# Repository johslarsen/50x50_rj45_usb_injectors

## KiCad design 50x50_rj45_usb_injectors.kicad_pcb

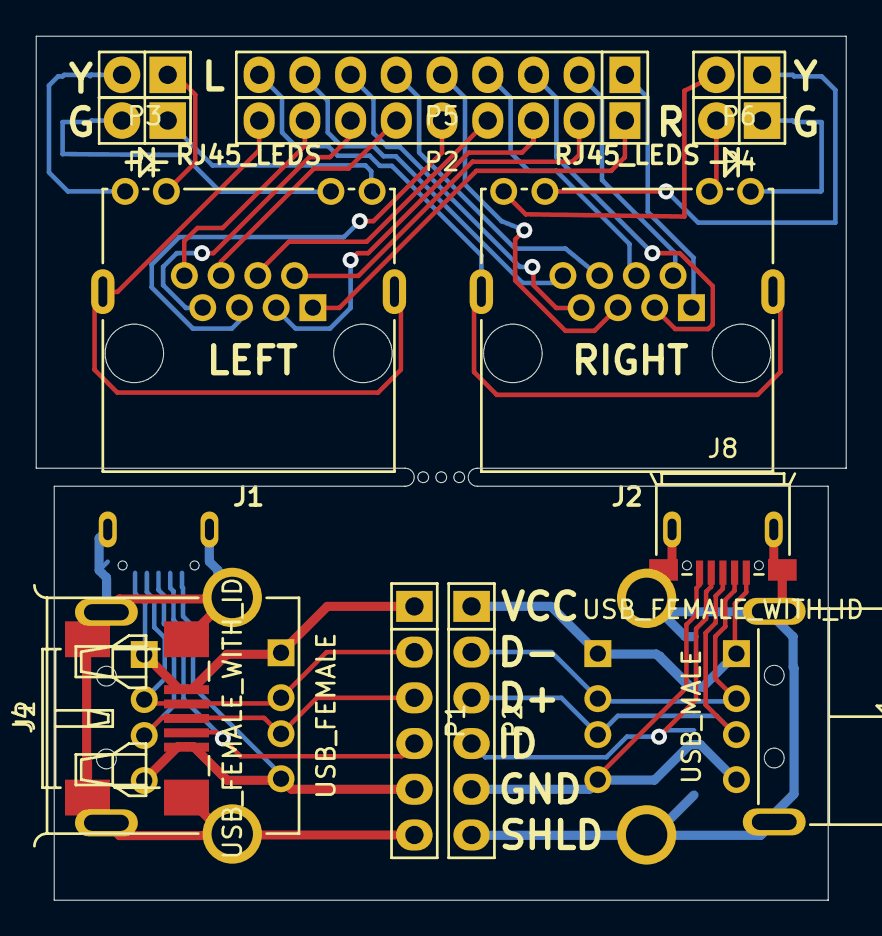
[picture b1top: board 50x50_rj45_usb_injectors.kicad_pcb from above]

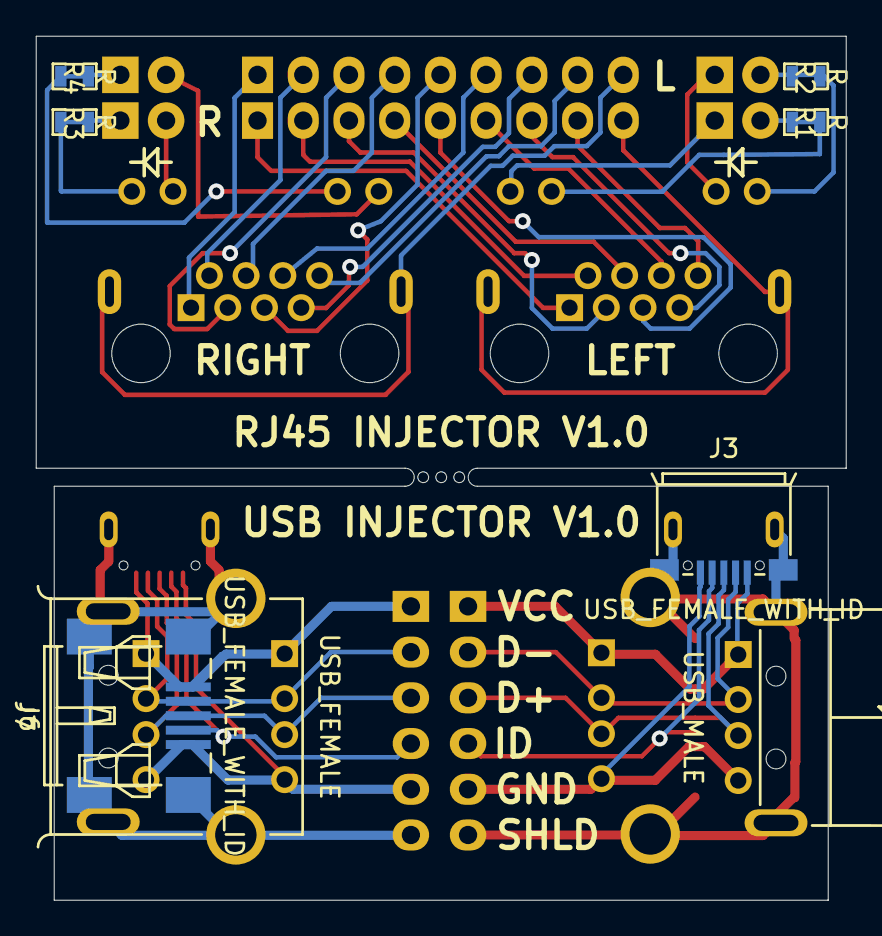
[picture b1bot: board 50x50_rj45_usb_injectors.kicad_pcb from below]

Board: 2 copper layers, 45.0 x 48.0 mm, 23 parts (8 on the bottom side), 33 nets.

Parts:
J1, J2: RJ45_LEDS; RJ45_LEDs
J1#2, J5: USB_MALE; USB_A_Male
J2#2, J6: USB_FEMALE; USB_A_Female
J3, J8: USB_FEMALE_WITH_ID; USB_Micro-B_Female_Wellco_AUSB_1011_05S2
J4, J7: USB_FEMALE_WITH_ID; USB_Mini-B_Female
Mouse_Bites_3_1mm: VAL**; Mouse_Bites_3_1mm
P1, P3, P4, P6: CONN_2; Pin_Header_Straight_1x02
P1#2, P2#2: CONN_6; Pin_Header_Straight_1x06
P2, P5: CONN_9; Pin_Header_Straight_1x09
R1, R2, R3, R4: R; SMD-0603_r

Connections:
unnamed: J1.1, J1#2.1, J2#2.1, J3.1, J4.1, P1#2.1, P2.1
unnamed: J1.2, J1#2.2, J2#2.2, J3.2, J4.2, P1#2.2, P2.2
unnamed: J1.3, J1#2.3, J2#2.3, J3.3, J4.3, P1#2.3, P2.3
unnamed: J1.4, J1#2.4, J2#2.4, J3.5, J4.5, P1#2.5, P2.4
unnamed: J1.5, J1#2.5, J2#2.5, J3.6, J4.6, P1#2.6, P2.5
unnamed: J1.6, P2.6
unnamed: J1.7, P2.7
unnamed: J1.8, P2.8
unnamed: J1.13, P2.9
unnamed: J1.GA, P1.2, R1.1, R1.2
unnamed: J1.GK, P1.1
unnamed: J1.YA, P3.2, R2.1, R2.2
unnamed: J1.YK, P3.1
unnamed: J2.1, P5.1
unnamed: J2.2, P5.2
unnamed: J2.3, P5.3
unnamed: J2.4, P5.4
unnamed: J2.5, P5.5
unnamed: J2.6, P5.6
unnamed: J2.7, P5.7
unnamed: J2.8, P5.8
unnamed: J2.13, P5.9
unnamed: J2.GA, P4.2
unnamed: J2.GK, P4.1, R3.1, R3.2
unnamed: J2.YA, P6.2
unnamed: J2.YK, P6.1, R4.1, R4.2
unnamed: J3.4, J4.4, P1#2.4
unnamed: J5.1, J6.1, J7.1, J8.1, P2#2.1
unnamed: J5.2, J6.2, J7.2, J8.2, P2#2.2
unnamed: J5.3, J6.3, J7.3, J8.3, P2#2.3
unnamed: J5.4, J6.4, J7.5, J8.5, P2#2.5
unnamed: J5.5, J6.5, J7.6, J8.6, P2#2.6
unnamed: J7.4, J8.4, P2#2.4

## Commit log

2015-01-11 added UNLICENSE
2015-01-11 added lib/Misc.pretty submodule
2015-01-11 created a board containing USB and RJ45 injectors joined by some 1mm mouse bites
2015-01-14 rounded the corners of the subboards
2015-01-14 changed to relative submodules
2015-01-14 added subboards as submodules
2015-02-07 added output for v1.0
